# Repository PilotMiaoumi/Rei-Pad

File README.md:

# RP-00
A custom macropad with a 3x3 matrix of switches, a 0.91" I2C OLED display, and 12 SK6182 LEDs all powered by a Seeed XIAO RP2040 DIP.

This project was designed and modeled entirely for the Hack Club Blueprint program.

## Features
```
Quick Phrase - Types "I hate kittens."
Save - Sends CTRL + S
LEDTOG - Turns LEDs on or off

Quick Email - Types your email
Copy - Sends CTRL + C
Paste - Sends CTRL + V

Num7 - Sends Num7
Cut - Sends CTRL + X
Num9 - Sends Num9
```

## Planned Features:
```
Interface with OLED Support
Options to create macros without having to code
WLED-like LED settings and animations
Clipboard Indicator
Icons & Animations
```

## System Layout
```
Switches:
Row 0 - GPIO26
Row 1 - GPIO27
Row 2 - GPIO28
Column 0 - GPIO2
Column 1 - GPIO4
Column 3 (woops i should fix that) - GPIO00

OLED
Pin 1 - GND
Pin 2 - 5V
Pin 3 - SCL (GPIO7)
Pin 4 - SDA (GPIO6)

RGBW LEDs (SK6812)
GPIO3 - LEDData (DIN)
Pin 1 DOUT - Pin 2 DIN
VDD - 5V
VSS - GND
```

## Structure
```
RP-00/
├── CAD/
│   ├── Bottom Case.step
│   ├── Top Case.step
│   └── Assembly.step
├── PCB/
│   ├── RP-00/
│   │   ├── RP-00.kicad_pro
│   │   ├── RP-00.kicad_sch
│   │   └── RP-00.kicad_pcb
│   ├── D+G/
│   │   ├── RP-00-B_Cu.gbr
│   │   ├── RP-00-B_Mask.gbr
│   │   ├── RP-00-B_Paste.gbr
│   │   ├── RP-00-B_Silkscreen.gbr
│   │   ├── RP-00-Edge_Cuts.gbr
│   │   ├── RP-00-F_Cu.gbr
│   │   ├── RP-00-F_Paste.gbr
│   │   ├── RP-00-F_Silkscreen.gbr
│   │   ├── RP-00-job.gbr.job
│   │   ├── RP-00-NPTH.drl
│   │   └── RP-00-PTH.drl
│   └── D+G.zip
├── Firmware/
│   └── main.py
├── Images/
│   ├── Assembly.png
│   ├── Bottom Case.png
│   ├── DRC 1.png
│   ├── DRC 2.png
│   ├── PCB Back.png
│   ├── PCB Front.png
│   ├── PCB Full.png
│   ├── Schematic.png
│   └── Top Case.png
└── README.md
```

## Screenshots

## Credits
Created by me (Miaoumi)

Made with KiCad, Autodesk Fusion

thanks hack club for funding

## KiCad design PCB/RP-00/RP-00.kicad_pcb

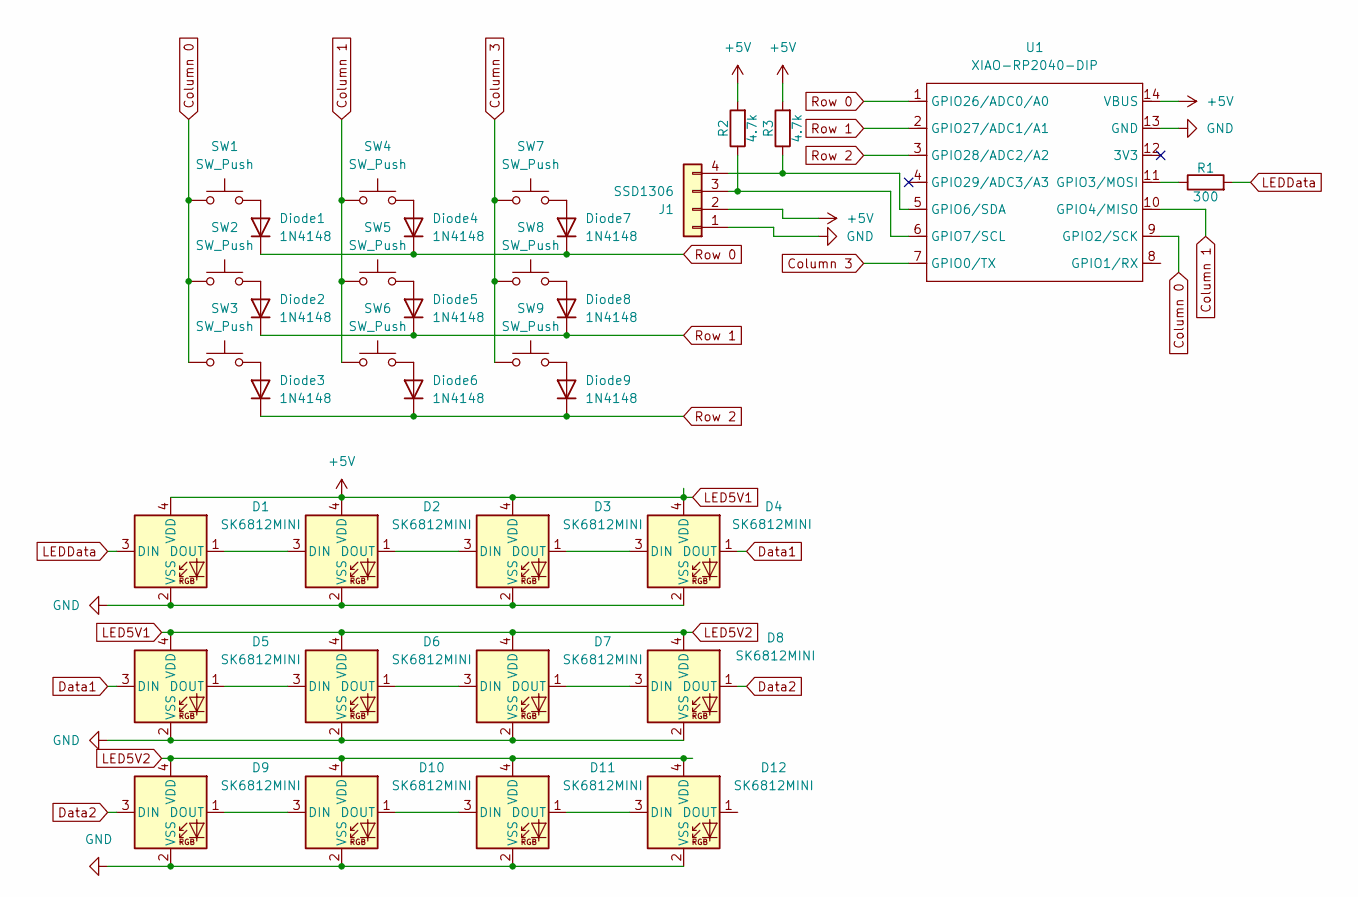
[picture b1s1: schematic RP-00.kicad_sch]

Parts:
D1, D2, D3, D4, D5, D6, D7, D8, D9, D10, D11, D12: SK6812MINI; LED_SK6812MINI_PLCC4_3.5x3.5mm_P1.75mm
Diode1, Diode2, Diode3, Diode4, Diode5, Diode6, Diode7, Diode8, Diode9: 1N4148; D_DO-35_SOD27_P7.62mm_Horizontal
J1: SSD1306; SSD1306-0.91-OLED-4pin-128x32
R1: 300; R_Axial_DIN0204_L3.6mm_D1.6mm_P5.08mm_Horizontal
R2, R3: 4.7k; R_Axial_DIN0204_L3.6mm_D1.6mm_P5.08mm_Horizontal
SW1, SW2, SW3, SW4, SW5, SW6, SW7, SW8, SW9: SW_Push; SW_Cherry_MX_1.00u_PCB
U1: XIAO-RP2040-DIP

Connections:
Column 0: SW1.1, SW2.1, SW3.1, U1.9 (GPIO2/SCK)
Column 1: SW4.1, SW5.1, SW6.1, U1.10 (GPIO4/MISO)
Column 3: SW7.1, SW8.1, SW9.1, U1.7 (GPIO0/TX)
Data1: D4.1 (DOUT), D5.3 (DIN)
Data2: D8.1 (DOUT), D9.3 (DIN)
GND: D1.2 (VSS), D2.2 (VSS), D3.2 (VSS), D4.2 (VSS), D5.2 (VSS), D6.2 (VSS), D7.2 (VSS), D8.2 (VSS), D9.2 (VSS), D10.2 (VSS), D11.2 (VSS), D12.2 (VSS), J1.1, U1.13 (GND)
LED5V1: D1.4 (VDD), D2.4 (VDD), D3.4 (VDD), D4.4 (VDD), D5.4 (VDD), D6.4 (VDD), D7.4 (VDD), D8.4 (VDD), D9.4 (VDD), D10.4 (VDD), D11.4 (VDD), D12.4 (VDD), J1.2, R2.2, R3.2, U1.14 (VBUS)
LEDData: D1.3 (DIN), R1.2
unnamed: D1.1 (DOUT), D2.3 (DIN)
unnamed: D2.1 (DOUT), D3.3 (DIN)
unnamed: D3.1 (DOUT), D4.3 (DIN)
unnamed: D5.1 (DOUT), D6.3 (DIN)
unnamed: D6.1 (DOUT), D7.3 (DIN)
unnamed: D7.1 (DOUT), D8.3 (DIN)
unnamed: D9.1 (DOUT), D10.3 (DIN)
unnamed: D10.1 (DOUT), D11.3 (DIN)
unnamed: D11.1 (DOUT), D12.3 (DIN)
unnamed: Diode1.2 (A), SW1.2
unnamed: Diode2.2 (A), SW2.2
unnamed: Diode3.2 (A), SW3.2
unnamed: Diode4.2 (A), SW4.2
unnamed: Diode5.2 (A), SW5.2
unnamed: Diode6.2 (A), SW6.2
unnamed: Diode7.2 (A), SW7.2
unnamed: Diode8.2 (A), SW8.2
unnamed: Diode9.2 (A), SW9.2
unnamed: J1.3, R2.1, U1.6 (GPIO7/SCL)
unnamed: J1.4, R3.1, U1.5 (GPIO6/SDA)
unnamed: R1.1, U1.11 (GPIO3/MOSI)
Row 0: Diode1.1 (K), Diode4.1 (K), Diode7.1 (K), U1.1 (GPIO26/ADC0/A0)
Row 1: Diode2.1 (K), Diode5.1 (K), Diode8.1 (K), U1.2 (GPIO27/ADC1/A1)
Row 2: Diode3.1 (K), Diode6.1 (K), Diode9.1 (K), U1.3 (GPIO28/ADC2/A2)

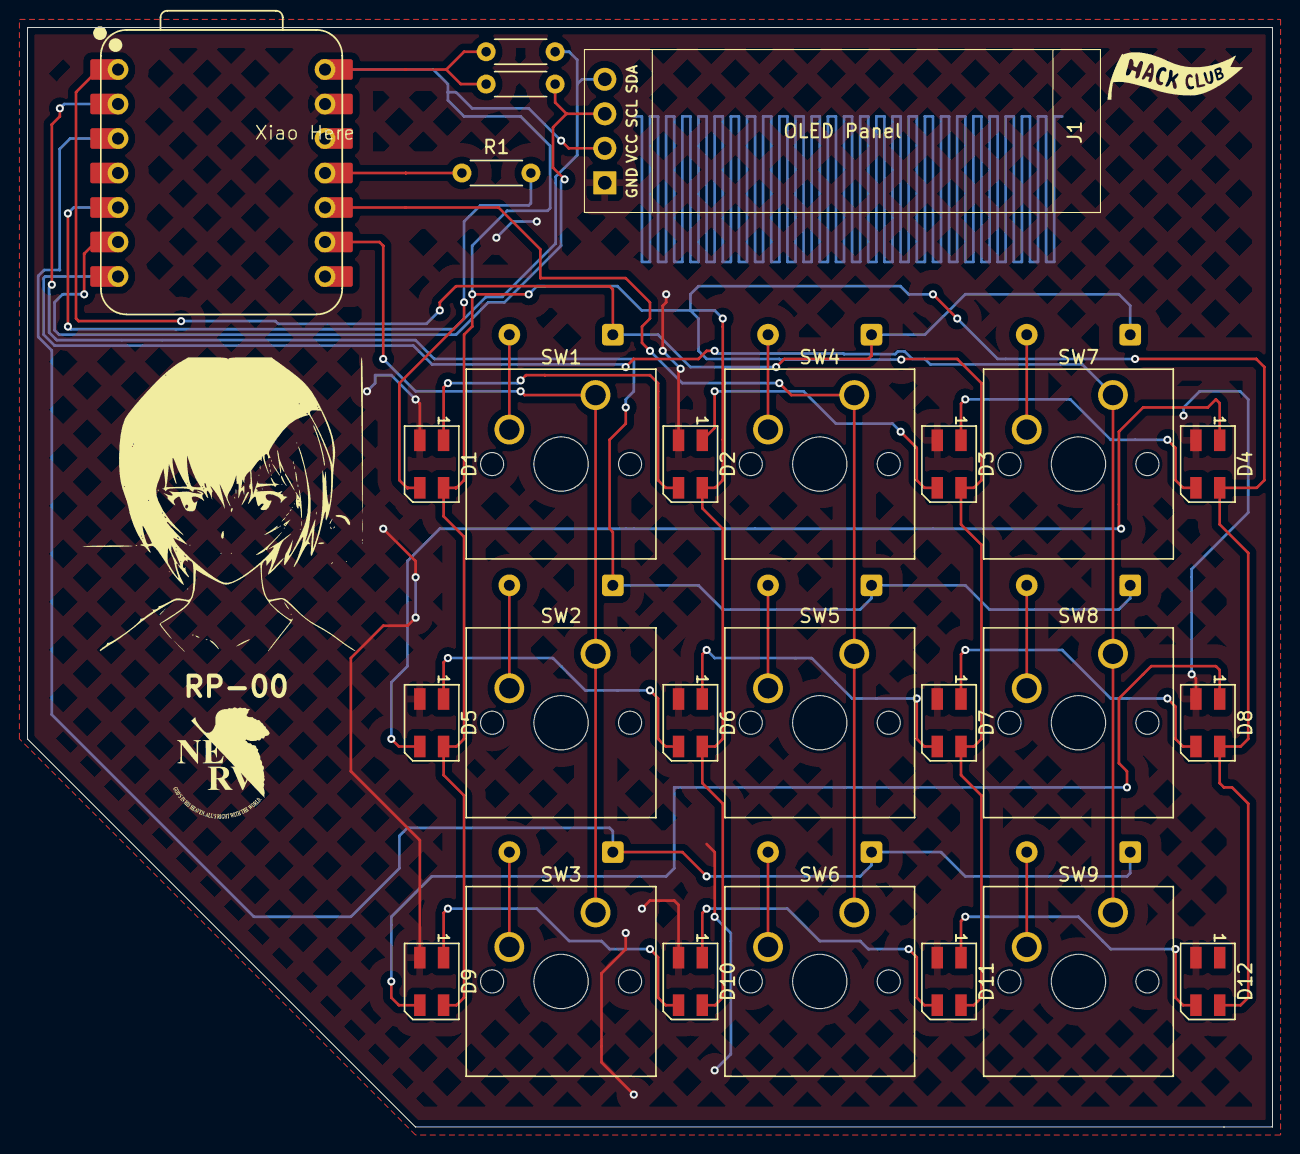
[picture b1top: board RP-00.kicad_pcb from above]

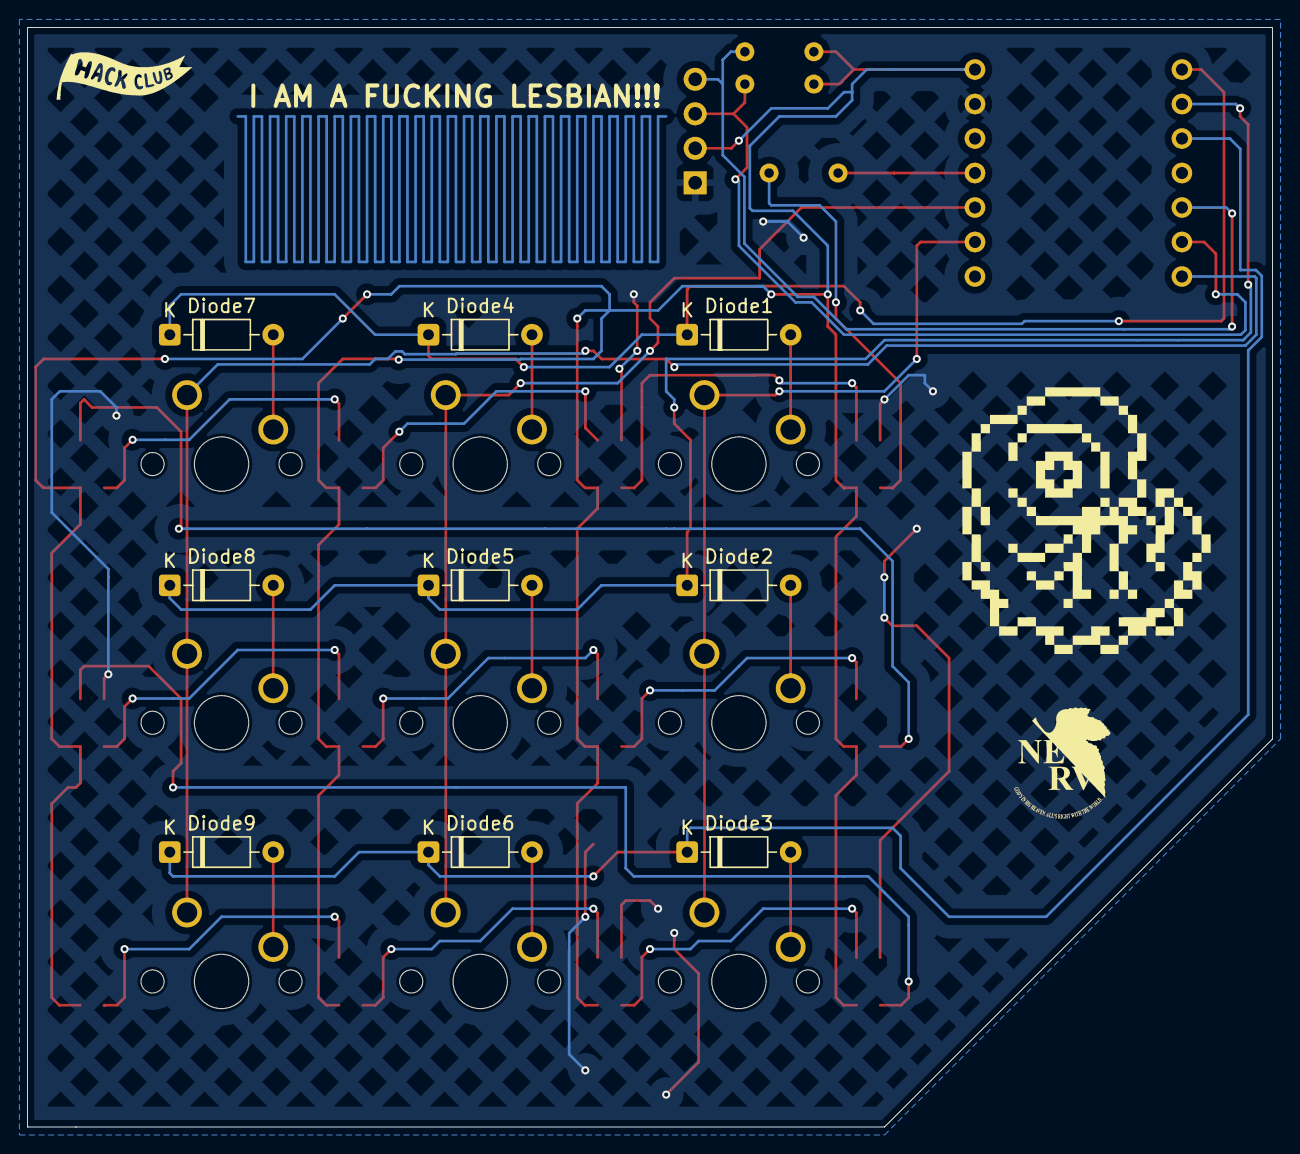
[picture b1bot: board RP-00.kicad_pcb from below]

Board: 2 copper layers, 91.7 x 81.0 mm, 35 parts (9 on the bottom side), 32 nets.

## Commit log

2025-12-05 Ported over full project.
2025-12-06 i made readme
2025-12-06 whoops
2025-12-06 Fixed Screenshots
2025-12-06 Fixed Formatting
2025-12-07 Added Gerber and Drill files
2025-12-07 Added Gerber and Drill structures to README
